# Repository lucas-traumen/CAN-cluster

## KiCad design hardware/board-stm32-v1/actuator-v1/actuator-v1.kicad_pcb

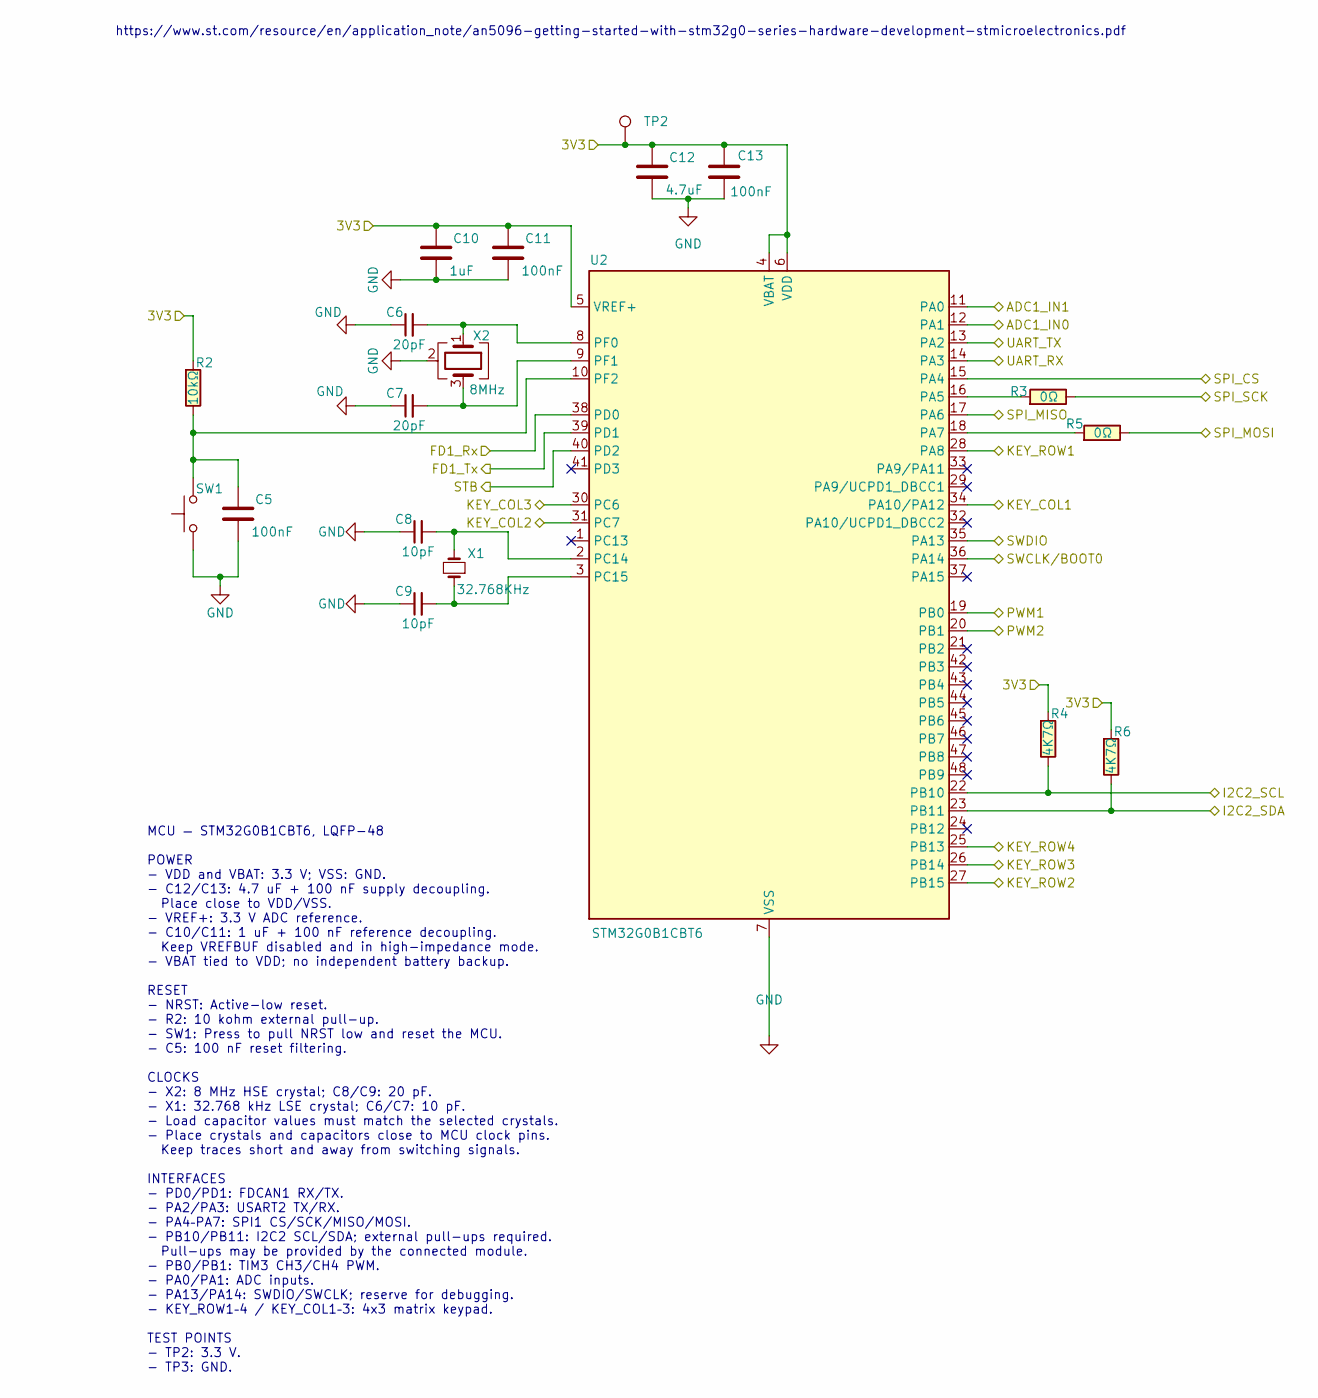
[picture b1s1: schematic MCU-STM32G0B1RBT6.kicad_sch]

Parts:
C5, C11, C13: 100nF; C_0603
C6, C7: 20pF; C_0603
C8, C9: 10pF; C_0603
C10: 1uF; C_0603
C12: 4.7uF; C_0603
R2: 10kΩ; R_0603
R3, R5: 0Ω; R_0603
R4, R6: 4K7Ω; R_0603
SW1: SW_Push; SW_SPST_CK_RS282G05A3
TP2: TestPoint; TestPoint_Pad_D1.5mm
U2: STM32G0B1CBT6; LQFP-48_7x7mm_P0.5mm
X1: 32.768KHz; Crystal_SMD_3215-2Pin_3.2x1.5mm
X2: 8MHz; Crystal_SMD_3225-4Pin_3.2x2.5mm

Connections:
/MCU-STM32G0B1CBT6/ADC1_IN0: U2.12 (PA1); also elsewhere on the board
/MCU-STM32G0B1CBT6/ADC1_IN1: U2.11 (PA0); also elsewhere on the board
/MCU-STM32G0B1CBT6/FD1_Rx: U2.38 (PD0); also elsewhere on the board
/MCU-STM32G0B1CBT6/FD1_Tx: U2.39 (PD1); also elsewhere on the board
/MCU-STM32G0B1CBT6/I2C2_SCL: R4.2, U2.22 (PB10); also elsewhere on the board
/MCU-STM32G0B1CBT6/I2C2_SDA: R6.2, U2.23 (PB11); also elsewhere on the board
/MCU-STM32G0B1CBT6/KEY_COL1: U2.34 (PA10/PA12); also elsewhere on the board
/MCU-STM32G0B1CBT6/KEY_COL2: U2.31 (PC7); also elsewhere on the board
/MCU-STM32G0B1CBT6/KEY_COL3: U2.30 (PC6); also elsewhere on the board
/MCU-STM32G0B1CBT6/KEY_ROW1: U2.28 (PA8); also elsewhere on the board
/MCU-STM32G0B1CBT6/KEY_ROW2: U2.27 (PB15); also elsewhere on the board
/MCU-STM32G0B1CBT6/KEY_ROW3: U2.26 (PB14); also elsewhere on the board
/MCU-STM32G0B1CBT6/KEY_ROW4: U2.25 (PB13); also elsewhere on the board
/MCU-STM32G0B1CBT6/PWM1: U2.19 (PB0); also elsewhere on the board
/MCU-STM32G0B1CBT6/PWM2: U2.20 (PB1); also elsewhere on the board
/MCU-STM32G0B1CBT6/SPI_CS: U2.15 (PA4); also elsewhere on the board
/MCU-STM32G0B1CBT6/SPI_MISO: U2.17 (PA6); also elsewhere on the board
/MCU-STM32G0B1CBT6/SPI_MOSI: R5.2; also elsewhere on the board
/MCU-STM32G0B1CBT6/SPI_SCK: R3.2; also elsewhere on the board
/MCU-STM32G0B1CBT6/STB: U2.40 (PD2); also elsewhere on the board
/MCU-STM32G0B1CBT6/SWCLK/BOOT0: U2.36 (PA14); also elsewhere on the board
/MCU-STM32G0B1CBT6/SWDIO: U2.35 (PA13); also elsewhere on the board
/MCU-STM32G0B1CBT6/UART_RX: U2.14 (PA3); also elsewhere on the board
/MCU-STM32G0B1CBT6/UART_TX: U2.13 (PA2); also elsewhere on the board
/Power5-3V3/+3V3: C10.1, C11.1, C12.1, C13.1, R2.1, R4.1, R6.1, TP2.1 (1_1), U2.4 (VBAT), U2.5 (VREF+), U2.6 (VDD); also elsewhere on the board
GND: C5.2, C6.1, C7.1, C8.1, C9.1, C10.2, C11.2, C12.2, C13.2, SW1.1, U2.7 (VSS), X2.2 (G), X2.4 (G); also elsewhere on the board
unnamed: R3.1, U2.16 (PA5)
unnamed: R5.1, U2.18 (PA7)
unnamed: C8.2, U2.2 (PC14), X1.2
unnamed: C9.2, U2.3 (PC15), X1.1
unnamed: C6.2, U2.8 (PF0), X2.1
unnamed: C7.2, U2.9 (PF1), X2.3
unnamed: C5.1, R2.2, SW1.2, U2.10 (PF2)

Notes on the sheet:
MCU — STM32G0B1CBT6, LQFP-48 POWER - VDD and VBAT: 3.3 V; VSS: GND. - C12/C13: 4.7 uF + 100 nF supply decoupling. Place close to VDD/VSS. - VREF+: 3.3 V ADC reference. - C10/C11: 1 uF + 100 nF reference decoupling. Keep VREFBUF disabled and in high-impedance mode. - VBAT tied to VDD; no independent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
https://www.st.com/resource/en/application_note/an5096-getting-started-with-stm32g0-series-hardware-development-stmicroelectronics.pdf

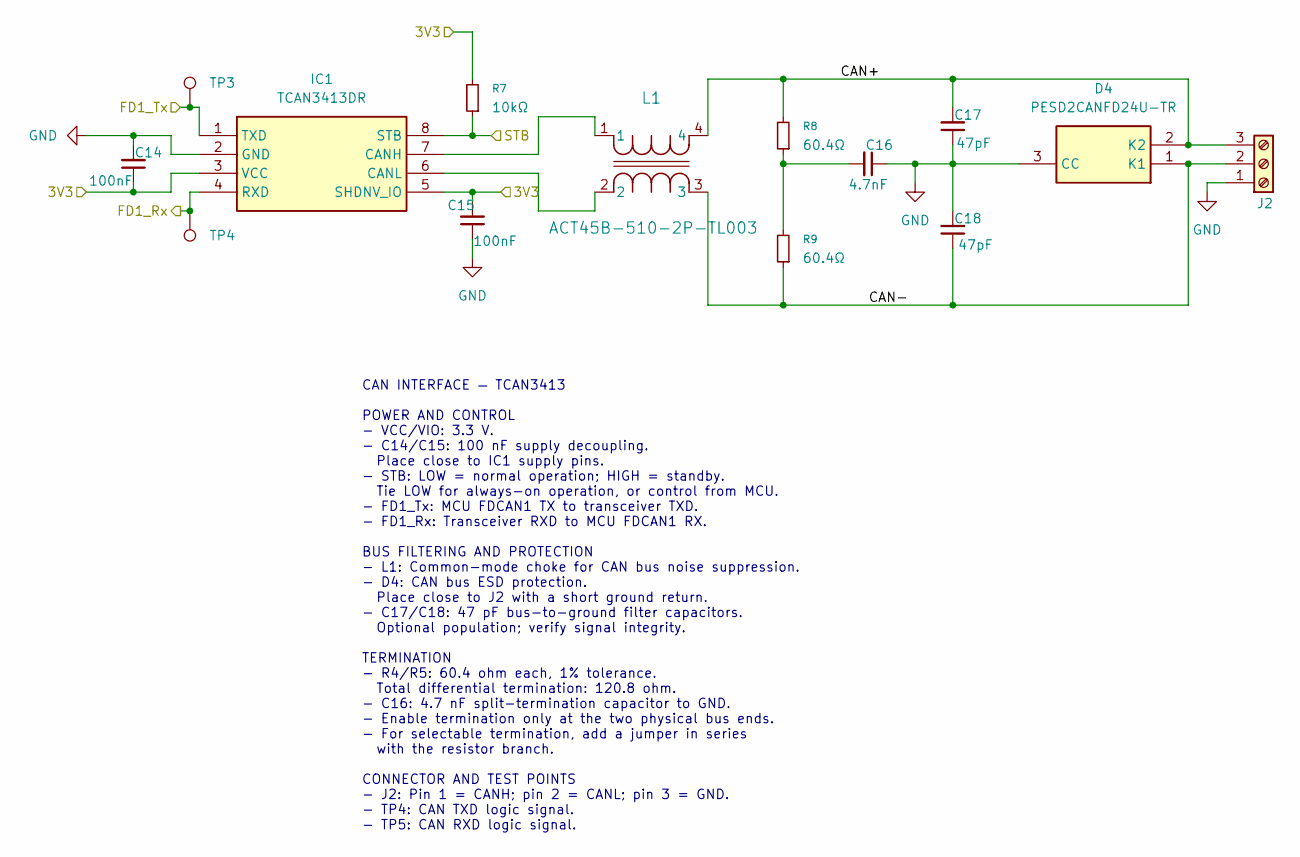
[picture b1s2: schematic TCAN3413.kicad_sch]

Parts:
C14, C15: 100nF; C_0603
C16: 4.7nF; C_0603
C17, C18: 47pF; C_0603
D4: PESD2CANFD24U-TR; SOT95P230X110-3N; Manufacturer_Part_Number PESD2CANFD24U-TR; Mouser Part Number 771-PESD2CANFD24U-TR
IC1: TCAN3413DR; SOIC127P600X175-8N; Manufacturer_Part_Number TCAN3413DR; Mouser Part Number 595-TCAN3413DR
J2: Screw_Terminal_01x03; PhoenixContact_MSTBA_2,5_3-G-5,08_1x03_P5.08mm_Horizontal
L1: ACT45B-510-2P-TL003; IND_ACT45R_TDK
R7: 10kΩ; R_0603
R8, R9: 60.4Ω; R_0805_2012Metric
TP3, TP4: TestPoint; TestPoint_Pad_D1.0mm

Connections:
/MCU-STM32G0B1CBT6/FD1_Rx: IC1.4 (RXD), TP4.1 (1_1); also elsewhere on the board
/MCU-STM32G0B1CBT6/FD1_Tx: IC1.1 (TXD), TP3.1 (1_1); also elsewhere on the board
/MCU-STM32G0B1CBT6/STB: IC1.8 (STB), R7.1; also elsewhere on the board
/Power5-3V3/+3V3: C14.1, C15.2, IC1.3 (VCC), IC1.5 (SHDNV_IO), R7.2; also elsewhere on the board
/TCAN3413/CAN+: C17.2, D4.2 (K2), J2.3, L1.4, R8.2
/TCAN3413/CAN-: C18.1, D4.1 (K1), J2.2, L1.3, R9.1
GND: C14.2, C15.1, C16.1, C17.1, C18.2, D4.3 (CC), IC1.2 (GND), J2.1; also elsewhere on the board
unnamed: C16.2, R8.1, R9.2
unnamed: IC1.7 (CANH), L1.1
unnamed: IC1.6 (CANL), L1.2

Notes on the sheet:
CAN INTERFACE — TCAN3413 POWER AND CONTROL - VCC/VIO: 3.3 V. - C14/C15: 100 nF supply decoupling. Place close to IC1 supply pins. - STB: LOW = normal operation; HIGH = standby. Tie LOW for always-on operation, or control from MCU. - FD1_Tx: MCU FDCAN1 TX to transceiver TXD. - FD1_Rx: Transceiver RX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

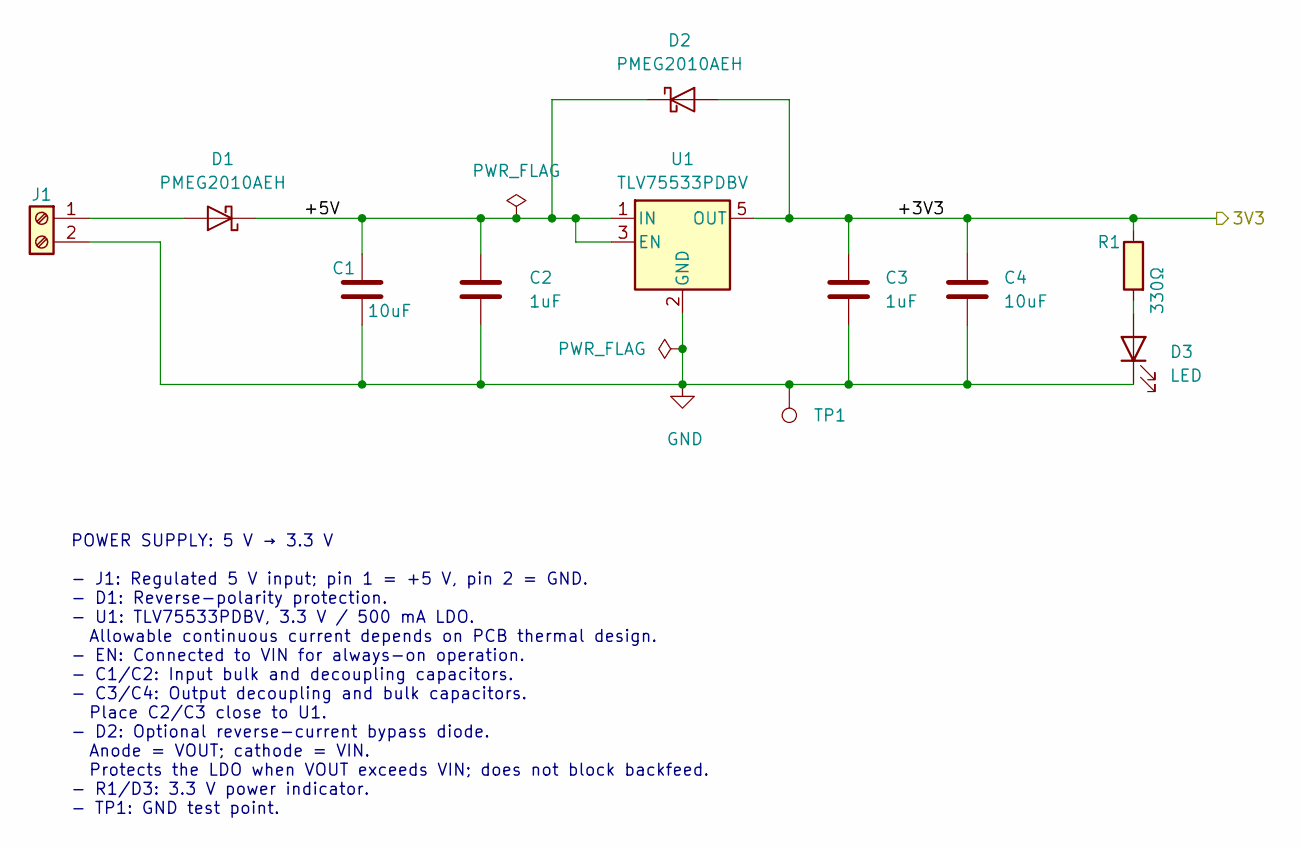
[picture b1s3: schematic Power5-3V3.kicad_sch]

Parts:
C1, C4: 10uF; C_0805_2012Metric_Pad1.18x1.45mm_HandSolder
C2, C3: 1uF; C_0603
D1, D2: PMEG2010AEH; D_SOD-123F
D3: LED; LED_0603_1608Metric
J1: Screw_Terminal_01x02; PhoenixContact_MSTBA_2,5_2-G-5,08_1x02_P5.08mm_Horizontal
R1: 330Ω; R_0603
TP1: TestPoint; TestPoint_Pad_D1.5mm
U1: TLV75533PDBV; SOT-23-5

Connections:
/Power5-3V3/+3V3: C3.1, C4.1, D2.2 (A), R1.2, U1.5 (OUT); also elsewhere on the board
/Power5-3V3/+5V: C1.1, C2.1, D1.1 (K), D2.1 (K), U1.1 (IN), U1.3 (EN)
GND: C1.2, C2.2, C3.2, C4.2, D3.1 (K), J1.2, TP1.1 (1_1), U1.2 (GND); also elsewhere on the board
unnamed: D1.2 (A), J1.1
unnamed: D3.2 (A), R1.1

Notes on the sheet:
POWER SUPPLY: 5 V → 3.3 V - J1: Regulated 5 V input; pin 1 = +5 V, pin 2 = GND. - D1: Reverse-polarity protection. - U1: TLV75533PDBV, 3.3 V / 500 mA LDO. Allowable continuous current depends on PCB thermal design. - EN: Connected to VIN for always-on operation. - C1/C2: Input bulk and decoupling c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

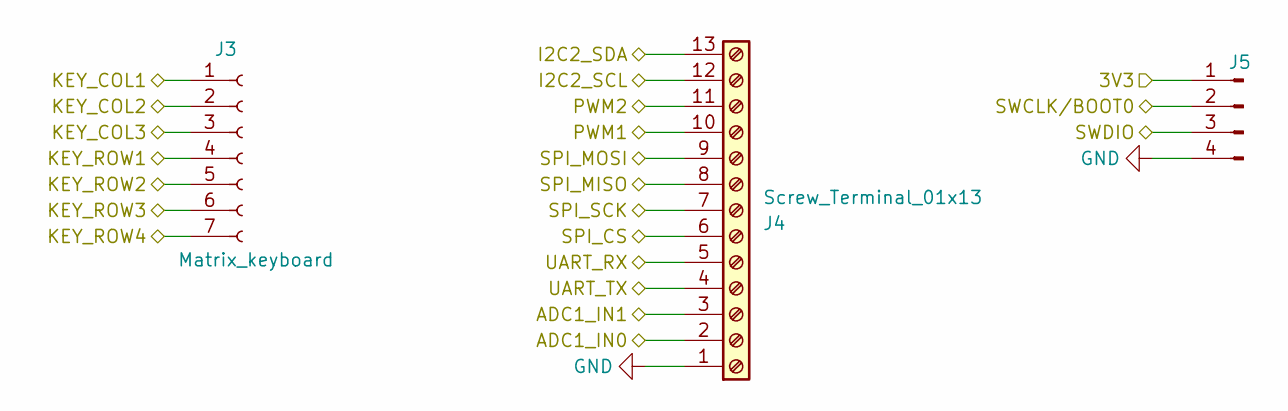
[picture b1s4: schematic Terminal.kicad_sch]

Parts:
J3: Matrix_keyboard; JST_XH_B7B-XH-A_1x07_P2.50mm_Vertical
J4: Screw_Terminal_01x13; PhoenixContact_MSTBA_2,5_13-G-5,08_1x13_P5.08mm_Horizontal
J5: Conn_01x04_Pin; PinHeader_1x04_P2.54mm_Vertical

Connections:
/MCU-STM32G0B1CBT6/ADC1_IN0: J4.2; also elsewhere on the board
/MCU-STM32G0B1CBT6/ADC1_IN1: J4.3; also elsewhere on the board
/MCU-STM32G0B1CBT6/I2C2_SCL: J4.12; also elsewhere on the board
/MCU-STM32G0B1CBT6/I2C2_SDA: J4.13; also elsewhere on the board
/MCU-STM32G0B1CBT6/KEY_COL1: J3.1; also elsewhere on the board
/MCU-STM32G0B1CBT6/KEY_COL2: J3.2; also elsewhere on the board
/MCU-STM32G0B1CBT6/KEY_COL3: J3.3; also elsewhere on the board
/MCU-STM32G0B1CBT6/KEY_ROW1: J3.4; also elsewhere on the board
/MCU-STM32G0B1CBT6/KEY_ROW2: J3.5; also elsewhere on the board
/MCU-STM32G0B1CBT6/KEY_ROW3: J3.6; also elsewhere on the board
/MCU-STM32G0B1CBT6/KEY_ROW4: J3.7; also elsewhere on the board
/MCU-STM32G0B1CBT6/PWM1: J4.10; also elsewhere on the board
/MCU-STM32G0B1CBT6/PWM2: J4.11; also elsewhere on the board
/MCU-STM32G0B1CBT6/SPI_CS: J4.6; also elsewhere on the board
/MCU-STM32G0B1CBT6/SPI_MISO: J4.8; also elsewhere on the board
/MCU-STM32G0B1CBT6/SPI_MOSI: J4.9; also elsewhere on the board
/MCU-STM32G0B1CBT6/SPI_SCK: J4.7; also elsewhere on the board
/MCU-STM32G0B1CBT6/SWCLK/BOOT0: J5.2; also elsewhere on the board
/MCU-STM32G0B1CBT6/SWDIO: J5.3; also elsewhere on the board
/MCU-STM32G0B1CBT6/UART_RX: J4.5; also elsewhere on the board
/MCU-STM32G0B1CBT6/UART_TX: J4.4; also elsewhere on the board
/Power5-3V3/+3V3: J5.1; also elsewhere on the board
GND: J4.1, J5.4; also elsewhere on the board

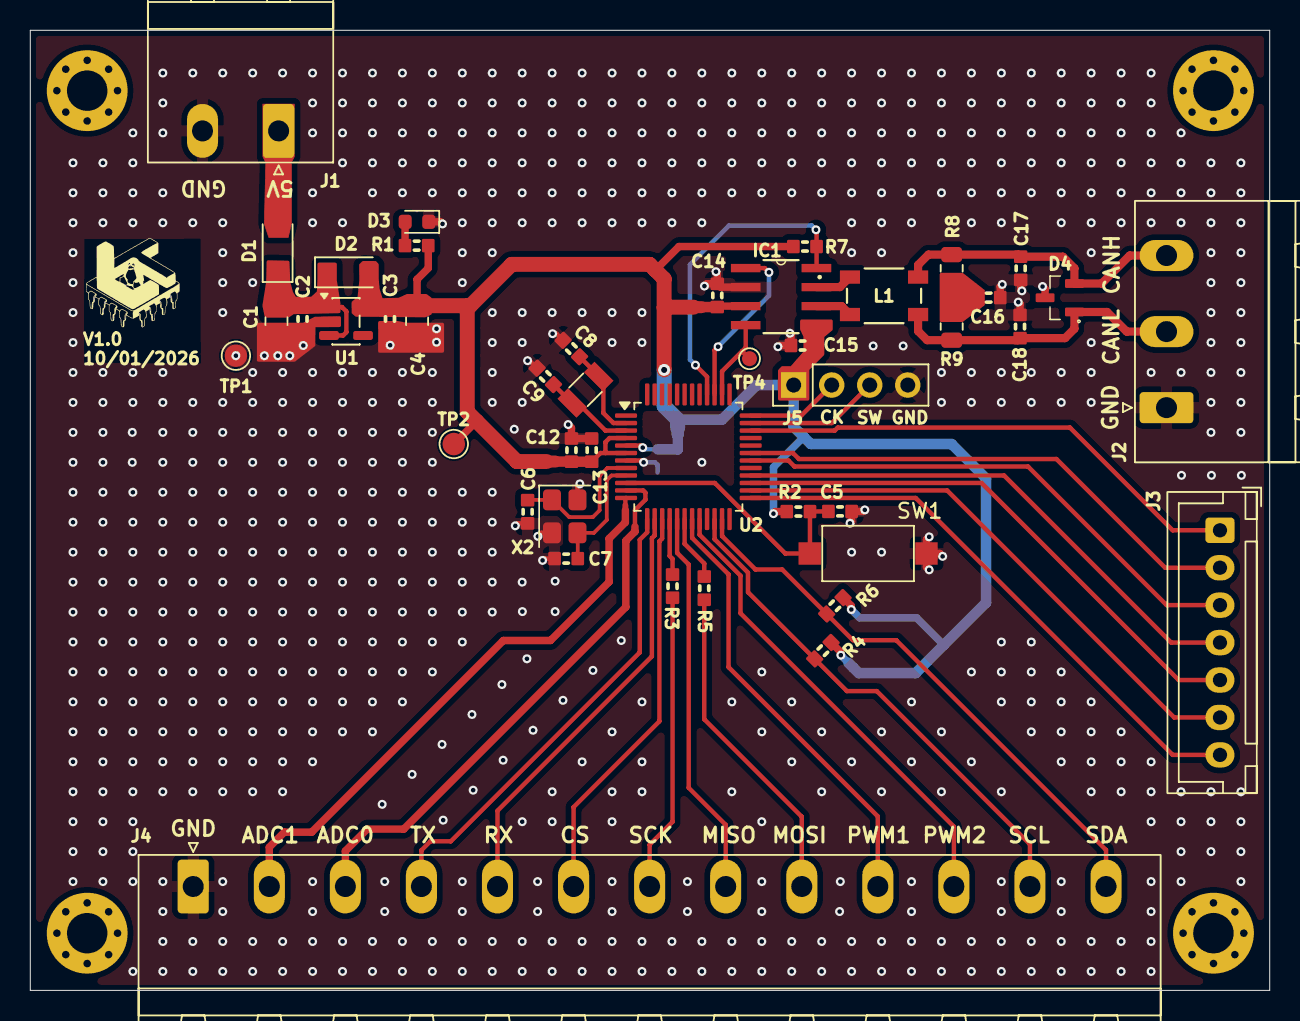
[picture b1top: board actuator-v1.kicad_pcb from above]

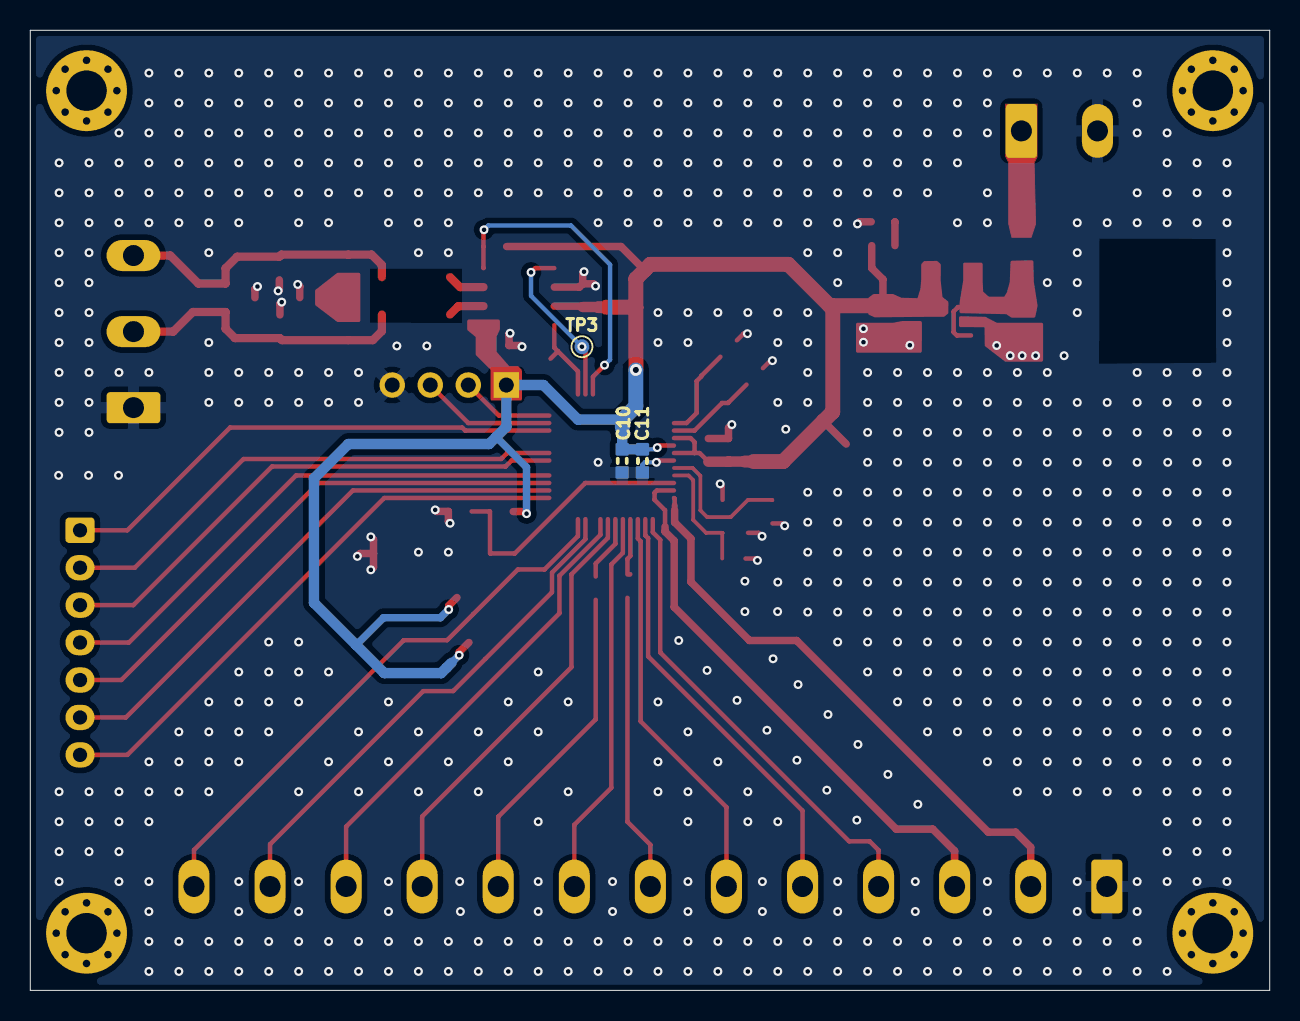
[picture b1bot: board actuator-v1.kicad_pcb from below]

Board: 2 copper layers, 82.8 x 64.1 mm, 47 parts (3 on the bottom side), 41 nets.
